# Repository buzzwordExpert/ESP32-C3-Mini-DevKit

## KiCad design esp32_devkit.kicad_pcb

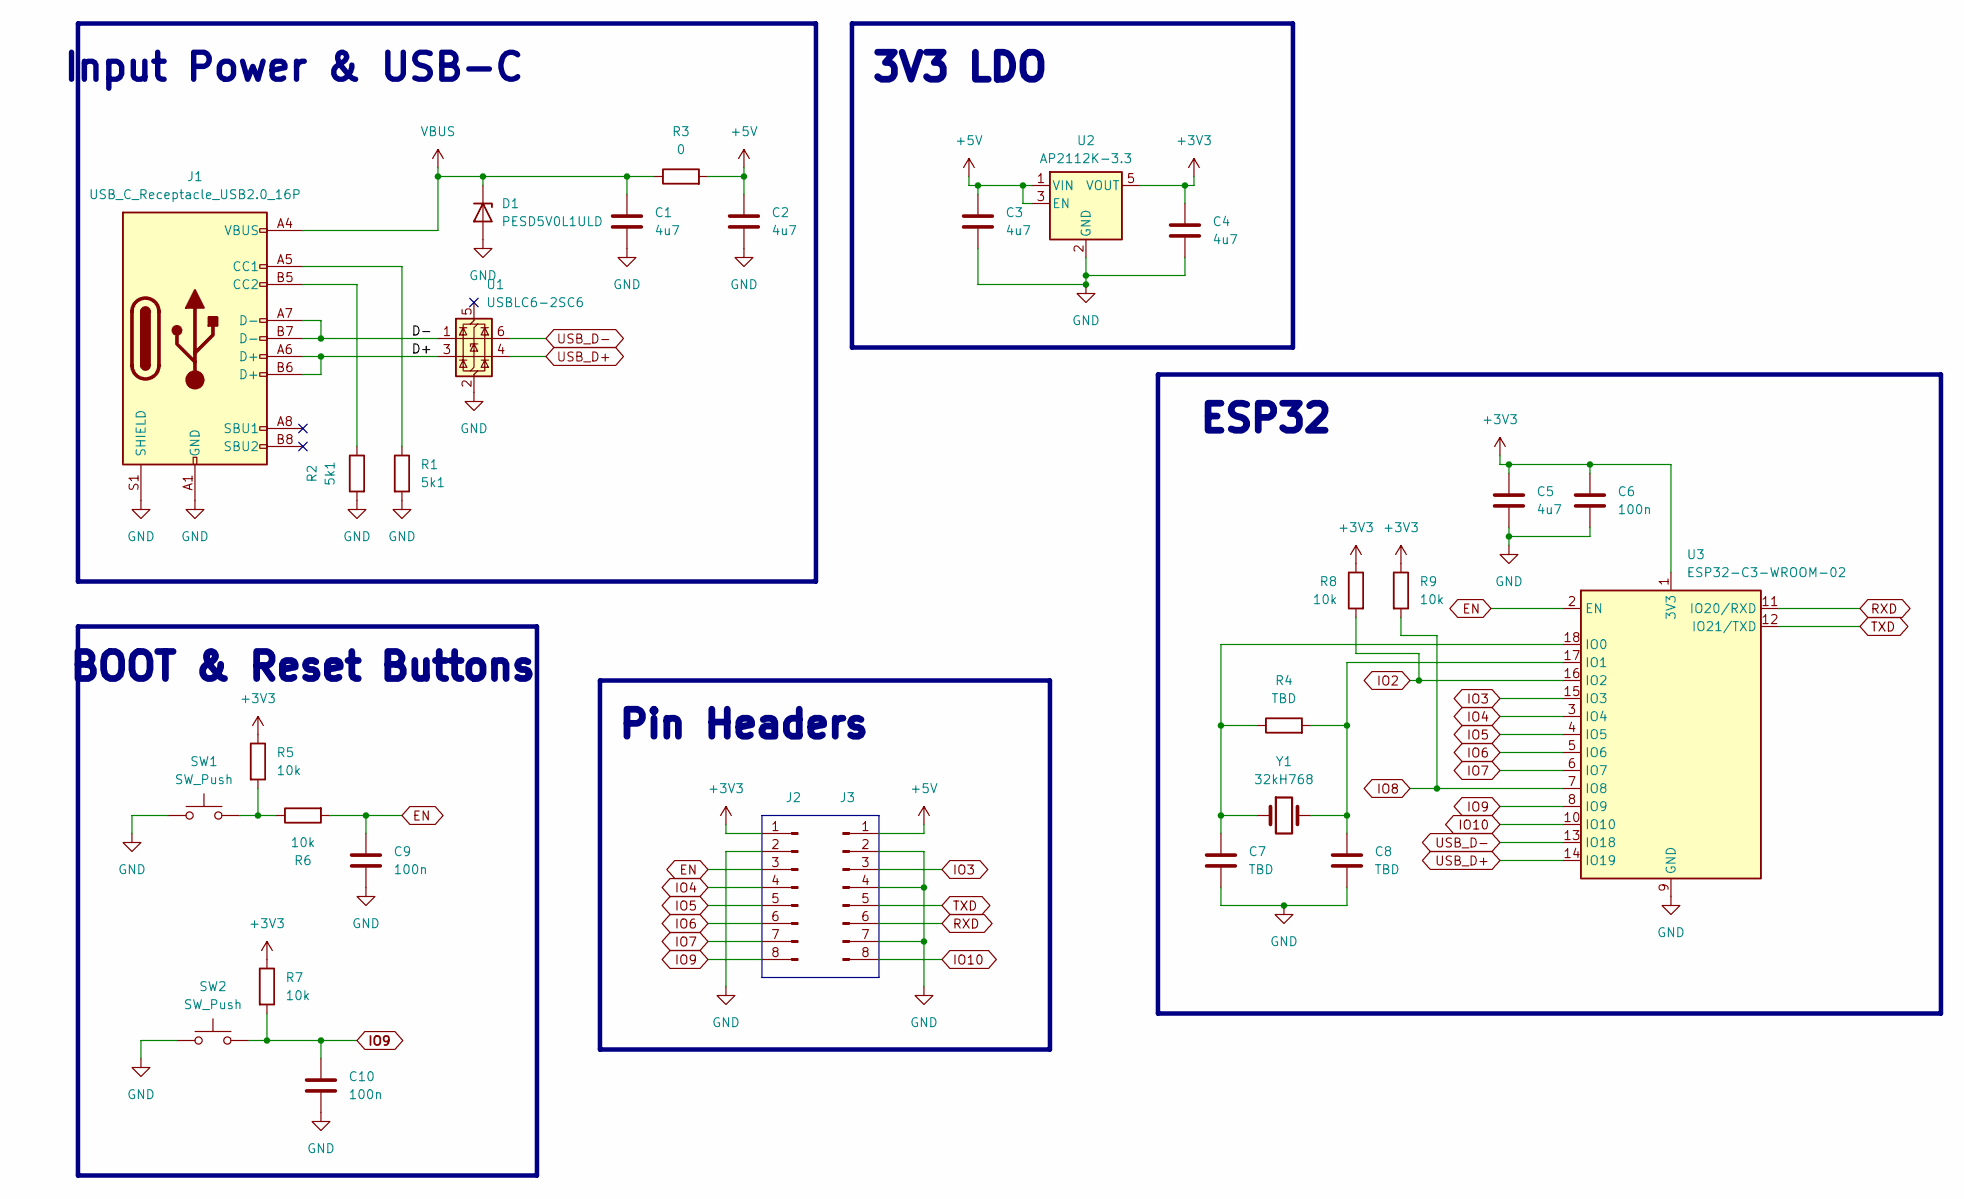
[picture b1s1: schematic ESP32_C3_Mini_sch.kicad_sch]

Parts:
C1, C2, C3, C4, C5: 4u7; C_0805_2012Metric
C6, C9, C10: 100n; C_0402_1005Metric
C7, C8: TBD; C_0201_0603Metric
D1: PESD5V0L1ULD; D_SOD-882D
J1: USB_C_Receptacle_USB2.0_16P; USB_C_Receptacle_G-Switch_GT-USB-7010ASV
J2, J3: Conn_01x08_Pin; PinHeader_1x08_P2.54mm_Horizontal
R1, R2: 5k1; R_0402_1005Metric
R3: 0; R_0805_2012Metric
R4: TBD; R_0201_0603Metric
R5, R6, R7, R8, R9: 10k; R_0402_1005Metric
SW1, SW2: SW_Push; SW_SPST_B3U-1000P
U1: USBLC6-2SC6; SOT-23-6
U2: AP2112K-3.3; SOT-23-5
U3: ESP32-C3-WROOM-02
Y1: 32kH768; Crystal_SMD_3215-2Pin_3.2x1.5mm

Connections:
+3V3: C4.1, C5.1, C6.1, J2.1, R5.1, R7.1, R8.1, R9.1, U2.5 (VOUT), U3.1 (3V3)
+5V: C2.1, C3.1, J3.1, R3.2, U2.1 (VIN), U2.3 (EN)
/ESP32-C3-Mini/D+: J1.A6 (D+), J1.B6 (D+), U1.3 (I/O2)
/ESP32-C3-Mini/D-: J1.A7 (D-), J1.B7 (D-), U1.1 (I/O1)
EN: C9.1, J2.3, R6.2, U3.2 (EN)
GND: C1.2, C2.2, C3.2, C4.2, C5.2, C6.2, C7.2, C8.2, C9.2, C10.2, D1.2 (A), J1.A1 (GND), J1.A12 (GND), J1.B1 (GND), J1.B12 (GND), J1.S1 (SHIELD), J2.2, J3.2, J3.4, J3.7, R1.2, R2.2, SW1.1, SW2.1, U1.2 (GND), U2.2 (GND), U3.9 (GND), U3.19 (GND)
IO2: R8.2, U3.16 (IO2)
IO3: J3.3, U3.15 (IO3)
IO4: J2.4, U3.3 (IO4)
IO5: J2.5, U3.4 (IO5)
IO6: J2.6, U3.5 (IO6)
IO7: J2.7, U3.6 (IO7)
IO8: R9.2, U3.7 (IO8)
IO9: C10.1, J2.8, R7.2, SW2.2, U3.8 (IO9)
IO10: J3.8, U3.10 (IO10)
unnamed: J1.A5 (CC1), R1.1
unnamed: J1.B5 (CC2), R2.1
unnamed: R5.2, R6.1, SW1.2
unnamed: C7.1, R4.1, U3.18 (IO0), Y1.1
unnamed: C8.1, R4.2, U3.17 (IO1), Y1.2
RXD: J3.6, U3.11 (IO20/RXD)
TXD: J3.5, U3.12 (IO21/TXD)
USB_D+: U1.4 (I/O2), U3.14 (IO19)
USB_D-: U1.6 (I/O1), U3.13 (IO18)
VBUS: C1.1, D1.1 (K), J1.A4 (VBUS), J1.A9 (VBUS), J1.B4 (VBUS), J1.B9 (VBUS), R3.1

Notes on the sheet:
Input Power & USB-C
3V3 LDO
Pin Headers
ESP32
BOOT & Reset Buttons

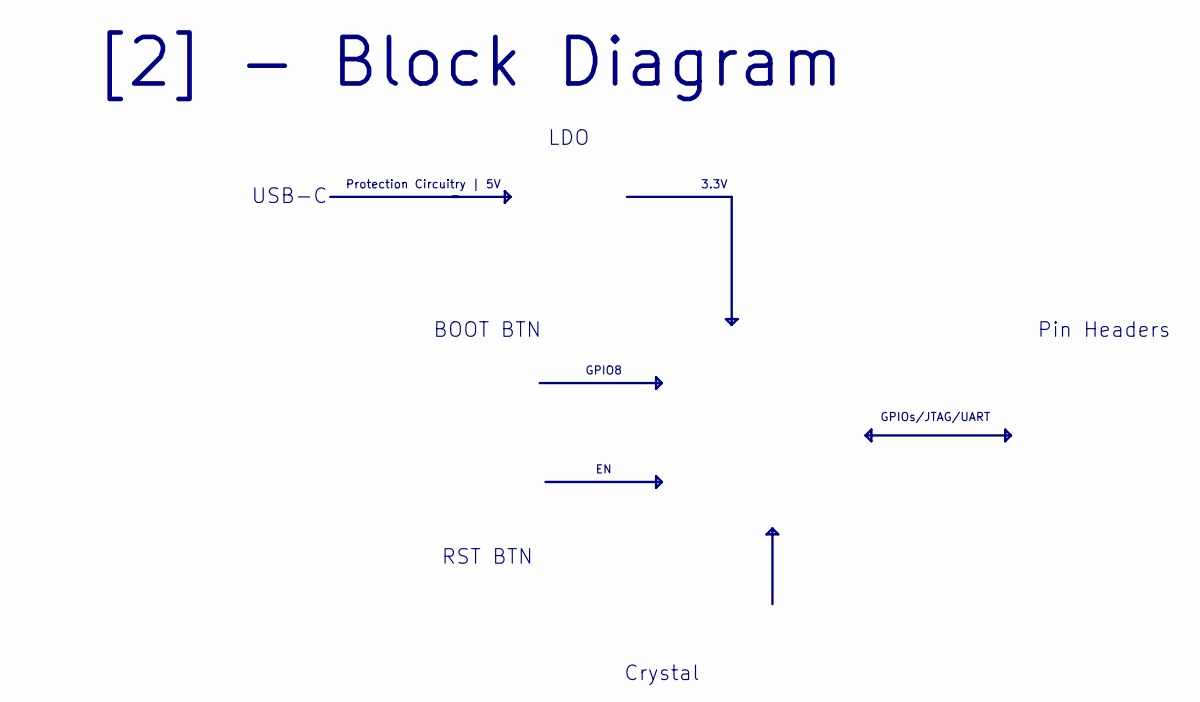
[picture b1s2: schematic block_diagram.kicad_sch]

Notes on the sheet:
GPIO8
LDO
BOOT BTN
USB-C
Pin Headers
Crystal
GPIOs/JTAG/UART
Protection Circuitry | 5V
3.3V
RST BTN
[2] - Block Diagram

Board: 2 copper layers, 29 parts (0 on the bottom side), 25 nets, no tracks yet.
